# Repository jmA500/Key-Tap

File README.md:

# Key-Tap

This little gadget can listen to the keyboard of an Amiga 500 and catch
certain hotkeys. These hotkeys can be used to drive output pins that can 
configure internal extentions. 

Please have a look at the project website:

https://www.jm27.de/key-tap-a-hardware-configurator-for-the-amiga-500/

# License

	All material is freely usable under the GPL v2

# Directory structure

	* hardware: Contains Eagle PCB files
	* firmware: Pre-built hex-files for different MCUs
	* src: the C-source code
	* doc: Documentation

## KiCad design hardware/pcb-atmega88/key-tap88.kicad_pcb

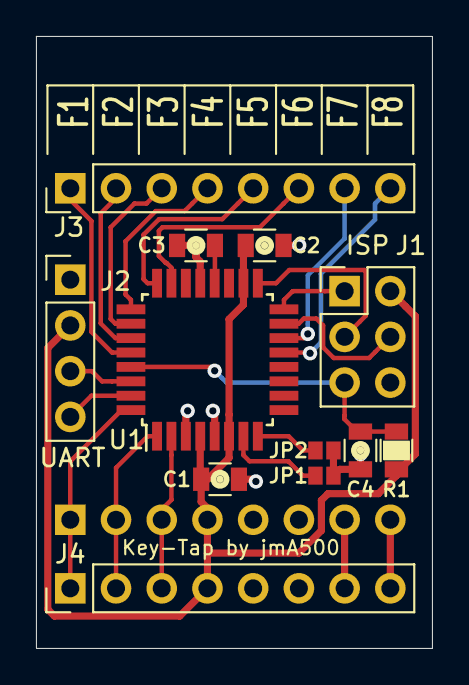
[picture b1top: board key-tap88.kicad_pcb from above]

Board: 2 copper layers, 22.0 x 34.0 mm, 13 parts (1 on the bottom side), 24 nets.

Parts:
C1, C2, C3, C4: 100n; C_0805
J1: AVR-ISP-6x; Pin_Header_Straight_2x03_Pitch2.54mm
J2: UART-CON-4; Pin_Header_Straight_1x04_Pitch2.54mm
J3: CONN_01X08; Pin_Header_Straight_1x08_Pitch2.54mm
J4: AMIGA-Keyboard-PINHEAD; Pin_Header_Straight_1x08_Pitch2.54mm
J5: AMIGA-Keyboard-PINHEAD; Socket_Strip_Straight_1x08_Pitch2.54mm
JP1, JP2: SolderJumper_2_Open; SMD-JUMPER
R1: 4k7; R_0805
U1: AtMega48PA; TQFP-32_7x7mm_Pitch0.8mm

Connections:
+5V: C1.1, C2.1, J1.2, J2.2, J4.4, J5.4, R1.1, U1.4, U1.6, U1.18
/MISO: J1.1, U1.16
/MOSI: J1.4, U1.15
/RXD: J2.3, U1.30
/SCK: J1.3, U1.17
/TXD: J2.4, U1.31
/~RESET: C4.2, J1.5, R1.2, U1.29
CF0: J3.1, U1.28
CF1: J3.2, U1.27
CF2: J3.3, U1.26
CF3: J3.4, U1.25
CF4: J3.5, U1.24
CF5: J3.6, U1.23
CF6: J3.7, U1.14
CF7: J3.8, U1.13
FLOPPY_LED: J4.8, J5.8
GND: C1.2, C2.2, C3.2, C4.1, J1.6, J2.1, J4.6, J5.6, JP1.1, JP2.1, U1.3, U1.5, U1.21
unnamed: C3.1, U1.20
unnamed: JP1.2, U1.7
unnamed: JP2.2, U1.8
POWER_LED: J4.7, J5.7
~KBCLK: J4.1, J5.1, U1.32
~KBDATA: J4.2, J5.2, U1.1
~KBRESET: J4.3, J5.3, U1.2

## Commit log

2021-03-13 Initil import
2021-03-13 Typo corrected
2021-03-25 * Added a new function to the generic version:
    To configure an RGBtoHDMI Adapter one needs to emulate short and long
    pushes to a push button. This is done on the last Config Pin (JP6 / pin 4)
    when Pushing F9 (short) or F10 (long) while Holding HELP.
    Caveat: UART debugging is untested
2021-03-25 Added firmware files.
2021-03-25 * Added new PCB version with Atmega88
2021-03-25 * Removed an old testing version of the source code * Source for new Atmega88 version will be added later
2021-03-26 * Added two solder Jumpers for Hardware configurability * Increased length of PCB tomake it sit on the DSUb connector in the back of an A500
2021-03-29 * Makefile: Deleted -y Flag for avrdude * main.c: Changed Timing for long press * uart4313.c: Used wrong buffer size
